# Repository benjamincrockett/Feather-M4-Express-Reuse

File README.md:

Index	Manufacturer Part Number	Manufacturer Name	Description	Lead Time	Availability	Stock Status	Attrition %	Requested Quantity 1	Pack Quantity 1	Pack Type 1	Digi-Key Part Number 1	Unit Price 1	Extended Price 1	Minimum Order Quantity 1	Customer Reference	Requested Part Number
1	    YC164-JR-07100KL	YAGEO	RES ARRAY 4 RES 100K OHM 1206		170,122	In Stock		1	1	Cut Tape (CT)	YC164J-100KCT-ND	0.10000	$0.10	1		YC164J-100KTR-ND
2	    DMP2045U-7	Diodes Incorporated	MOSFET P-CH 20V 4.3A SOT23		65,562	In Stock		1	1	Cut Tape (CT)	DMP2045U-7DICT-ND	0.17000	$0.17	1		DMP2045U-7DITR-ND
3	    MBR120VLSFT1G	onsemi	DIODE SCHOTTKY 20V 1A SOD123FL		110,035	In Stock		1	1	Cut Tape (CT)	MBR120VLSFT1GOSCT-ND	0.41000	$0.41	1		MBR120VLSFT1GOSTR-ND
4	    ABS07-32.768KHZ-T	Abracon LLC	CRYSTAL 32.7680KHZ 12.5PF SMD		938,078	In Stock		1	1	Cut Tape (CT)	535-9542-1-ND	0.61000	$0.61	1		535-9542-1-ND
5	    USB4105-GF-A	GCT	CONN RCP USB2.0 TYP C 24P SMD RA		23,931	In Stock		1	1	Cut Tape (CT)	2073-USB4105-GF-ACT-ND	0.78000	$0.78	1		2073-USB4105-GF-ACT-ND
6	    C0603C220J5GACTU	KEMET	CAP CER 22PF 50V C0G/NP0 0603		127,396	In Stock		2	2	Cut Tape (CT)	399-C0603C220J5GACTUCT-ND	0.12000	$0.24	1		399-C0603C220J5GACTUCT-ND
7	    C0805C106K8RACTU	KEMET	CAP CER 10UF 10V X7R 0805		615,848	In Stock		5	5	Cut Tape (CT)	399-C0805C106K8RACTUCT-ND	0.38000	$1.90	1		399-C0805C106K8RACTUCT-ND
8	    C0603C105K4RACTU	KEMET	CAP CER 1UF 16V X7R 0603		16,549	In Stock		6	6	Cut Tape (CT)	399-C0603C105K4RACTUCT-ND	0.08000	$0.48	1		399-C0603C105K4RACTUCT-ND
9	    LSQNA251818T100K	Taiyo Yuden	FIXED IND 10UH 820MA 325MOHM SMD		2,400	In Stock		1	1	Cut Tape (CT)	587-LSQNA251818T100KCT-ND	0.12000	$0.12	1		587-LSQNA251818T100KCT-ND
10	  RT0603FRE071KL	YAGEO	RES SMD 1K OHM 1% 1/10W 0603		146,547	In Stock		1	1	Cut Tape (CT)	YAG2323CT-ND	0.10000	$0.10	1		YAG2323CT-ND
11	  RC0603FR-075K1L	YAGEO	RES 5.1K OHM 1% 1/10W 0603		755,466	In Stock		3	3	Cut Tape (CT)	311-5.10KHRCT-ND	0.10000	$0.30	1		311-5.10KHRCT-ND
12	  AT0603FRE0710KL	YAGEO	RES SMD 10K OHM 1% 1/10W 0603		22,095	In Stock		5	5	Cut Tape (CT)	YAG2122CT-ND	0.10000	$0.50	1		YAG2122CT-ND
13	  AT0603FRE072K2L	YAGEO	RES SMD 2.2K OHM 1% 1/10W 0603		1,520	In Stock		1	1	Cut Tape (CT)	YAG2127CT-ND	0.16000	$0.16	1		YAG2127CT-ND
14	  Y78B21110FP	C&K	SWITCH TACTILE SPST-NO 0.05A 32V		136,536	In Stock		1	1	Cut Tape (CT)	401-1426-1-ND	0.59000	$0.59	1		401-1426-1-ND
15	  ATSAMD51J19A-MUT	Microchip Technology	IC MCU 32BIT 512KB FLASH 64VQFN		3,462	In Stock		1	1	Cut Tape (CT)	ATSAMD51J19A-MUTCT-ND	5.90000	$5.90	1		ATSAMD51J19A-MUTCT-ND
16	  MCP73831T-2ACI/OT	Microchip Technology	IC BATT CNTL LI-ION 1CEL SOT23-5	1 expected in stock on 10-Nov-2025	0	Normally Stocking		1	1	Cut Tape (CT)	MCP73831T-2ACI/OTCT-ND	0.76000	$0.76	1		MCP73831T-2ACI/OTCT-ND
17	AP2112K-3.3TRG1	Diodes Incorporated	IC REG LINEAR 3.3V 600MA SOT-25		34,831	In Stock		1	1	Cut Tape (CT)	AP2112K-3.3TRG1DICT-ND	0.22000	$0.22	1		AP2112K-3.3TRG1DICT-ND
18	S2B-PH-SM4-TB	JST Sales America Inc.	CONN HEADER SMD R/A 2POS 2MM		81,304	In Stock		1	1	Cut Tape (CT)	455-S2B-PH-SM4-TBCT-ND	0.48000	$0.48	1		455-S2B-PH-SM4-TBCT-ND
19	BM03B-SRSS-TB	JST Sales America Inc.	CONN HEADER SMD 3POS 1MM		5,309	In Stock		1	1	Cut Tape (CT)	455-BM03B-SRSS-TBCT-ND	0.45000	$0.45	1		455-BM03B-SRSS-TBCT-ND
20	SM03B-SRSS-TB	JST Sales America Inc.	CONN HEADER SMD R/A 3POS 1MM		19,673	In Stock		1	1	Cut Tape (CT)	455-SM03B-SRSS-TBCT-ND	0.44000	$0.44	1		455-SM03B-SRSS-TBCT-ND
21	SM04B-SRSS-TB	JST Sales America Inc.	CONN HEADER SMD R/A 4POS 1MM		37,322	In Stock		1	1	Cut Tape (CT)	455-SM04B-SRSS-TBCT-ND	0.50000	$0.50	1		455-SM04B-SRSS-TBCT-ND
22	KO EELP41.22-Q1S2-25-A8J8-020-R18	ams-OSRAM USA INC.	LED ORANGE DIFFUSED 0603 SMD		23,602	In Stock		1	1	Cut Tape (CT)	475-KOEELP41.22-Q1S2-25-A8J8-020-R18CT-ND	0.14000	$0.14	1		475-KOEELP41.22-Q1S2-25-A8J8-020-R18CT-ND
23	KR EELP41.22-Q1S1-36-A8J8-020-R18	ams-OSRAM USA INC.	LED RED DIFFUSED 0603 SMD		11,725	In Stock		1	1	Cut Tape (CT)	475-KREELP41.22-Q1S1-36-A8J8-020-R18CT-ND	0.14000	$0.14	1		475-KREELP41.22-Q1S1-36-A8J8-020-R18CT-ND
24	KT EELP41.12-S2U1-25-2X4Y-5-R18	ams-OSRAM USA INC.	LED GREEN DIFFUSED 0603 SMD		26,710	In Stock		1	1	Cut Tape (CT)	475-KTEELP41.12-S2U1-25-2X4Y-5-R18CT-ND	0.16000	$0.16	1		475-KTEELP41.12-S2U1-25-2X4Y-5-R18CT-ND
25	W25Q128JVSIQ TR	Winbond Electronics	IC FLASH 128MBIT SPI/QUAD 8SOIC		117,652	In Stock		1	1	Cut Tape (CT)	256-W25Q128JVSIQTRCT-ND	1.85000	$1.85	1		256-W25Q128JVSIQTRCT-ND
26	RMCF0603FT100R	Stackpole Electronics Inc	RES 100 OHM 1% 1/10W 0603		1,052,511	In Stock		2	2	Cut Tape (CT)	RMCF0603FT100RCT-ND	0.10000	$0.20	1		RMCF0603FT100RCT-ND
27	CRT0603-BY-1003ELF	Bourns Inc.	RES SMD 100K OHM 0.1% 1/10W 0603		206,819	In Stock		3	3	Cut Tape (CT)	CRT0603-BY-1003ELFCT-ND	0.10000	$0.30	1		CRT0603-BY-1003ELFCT-ND

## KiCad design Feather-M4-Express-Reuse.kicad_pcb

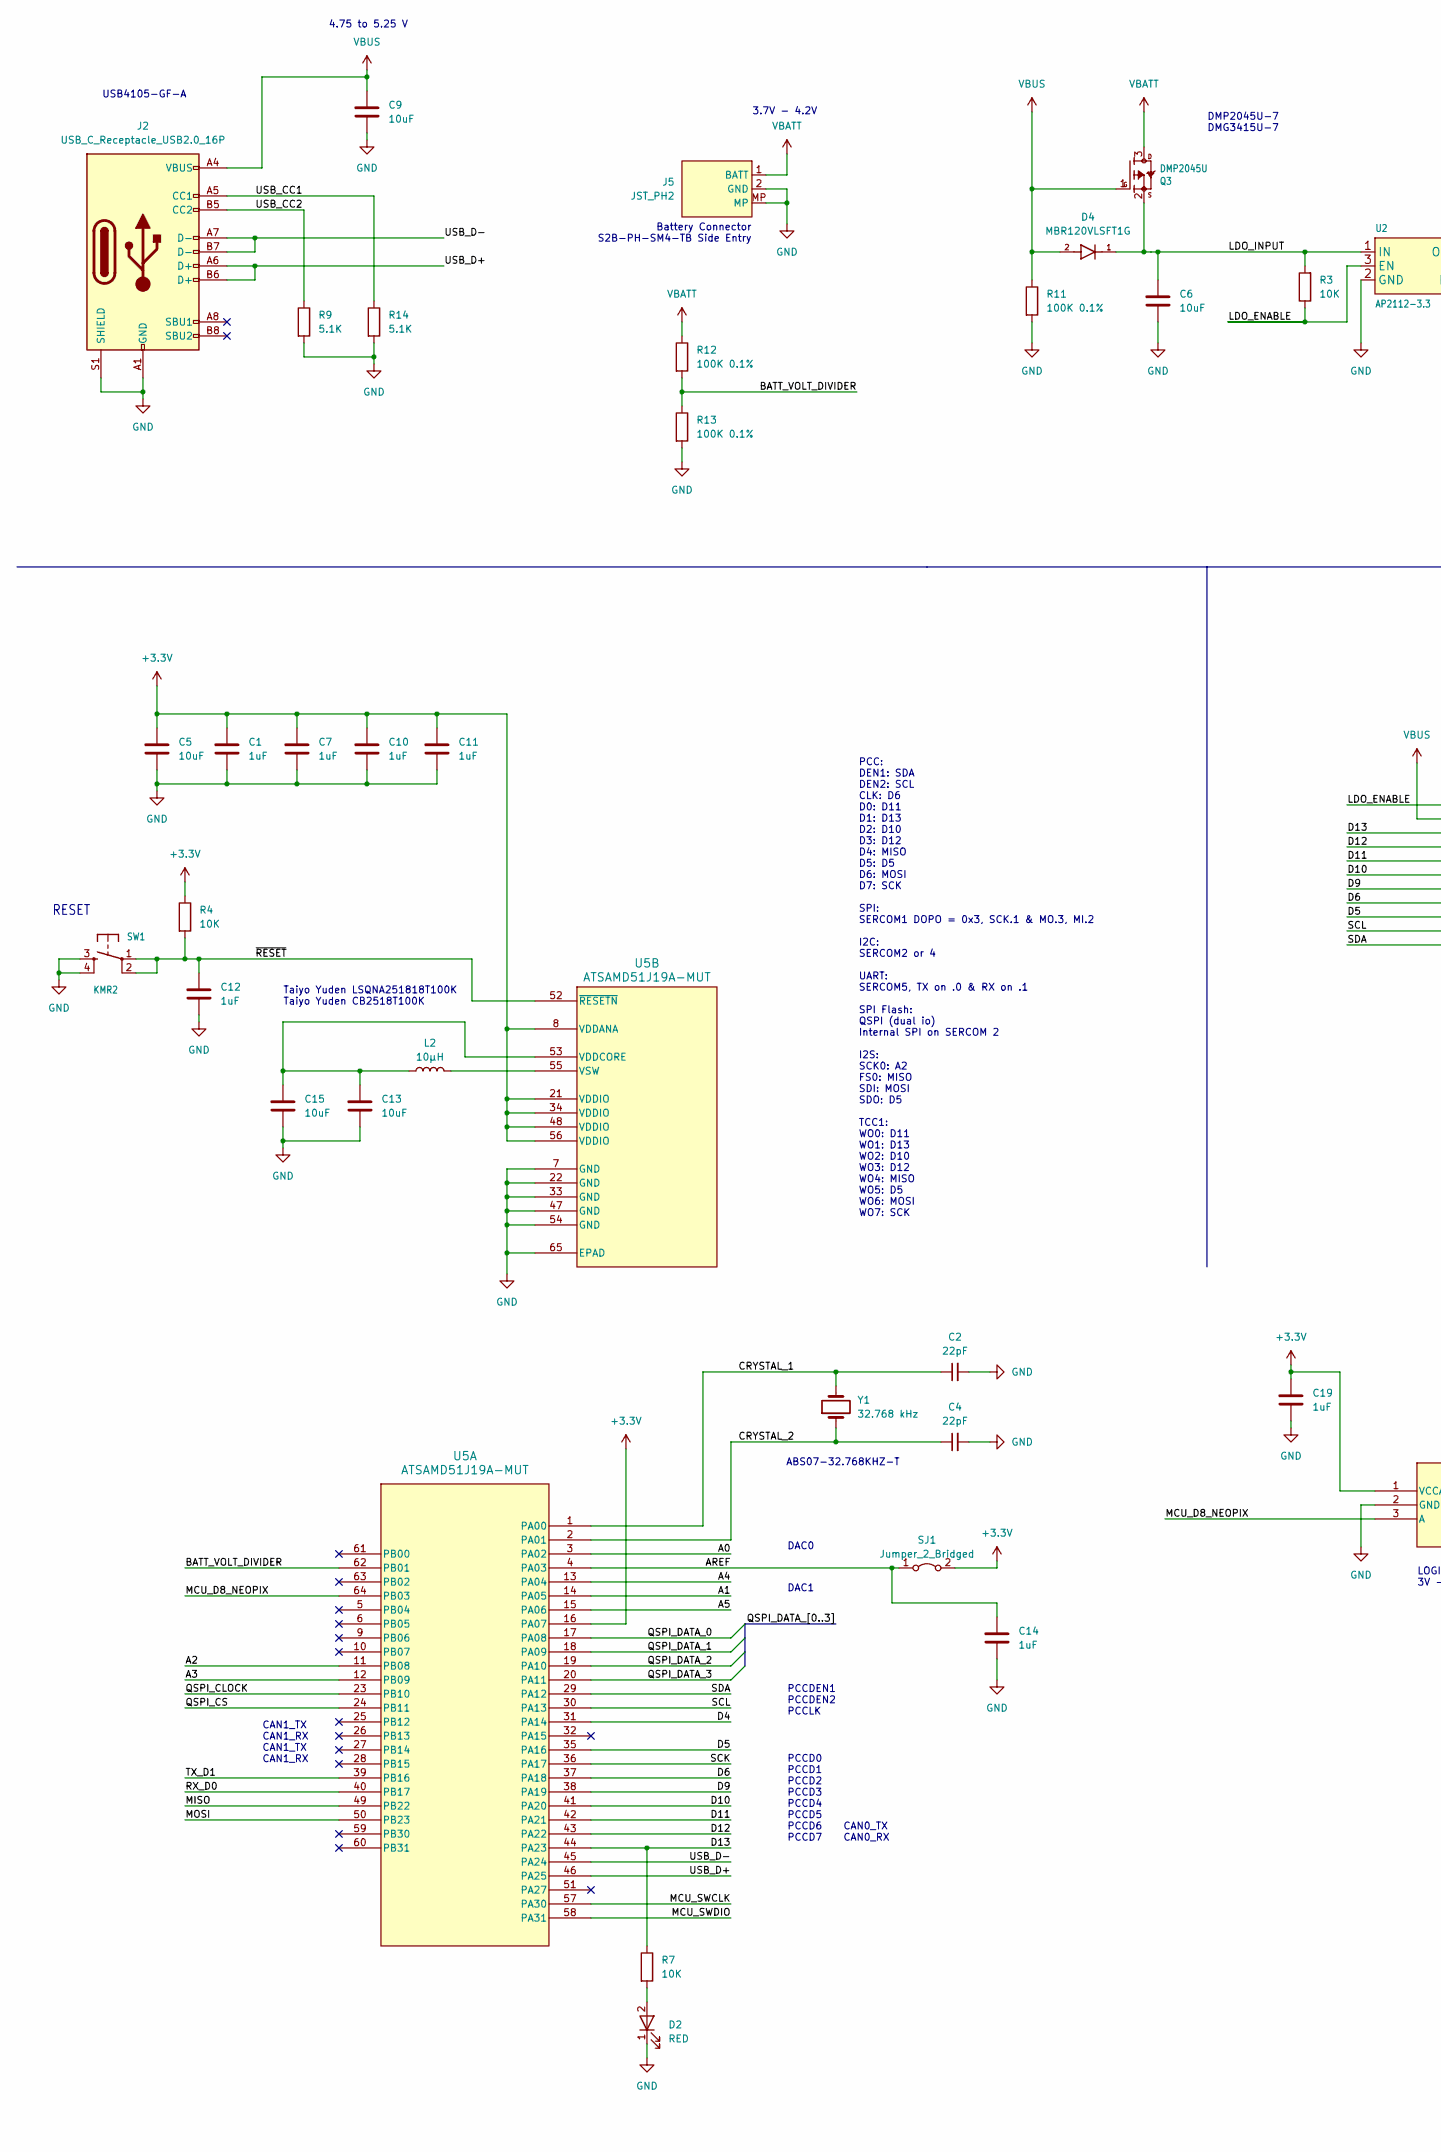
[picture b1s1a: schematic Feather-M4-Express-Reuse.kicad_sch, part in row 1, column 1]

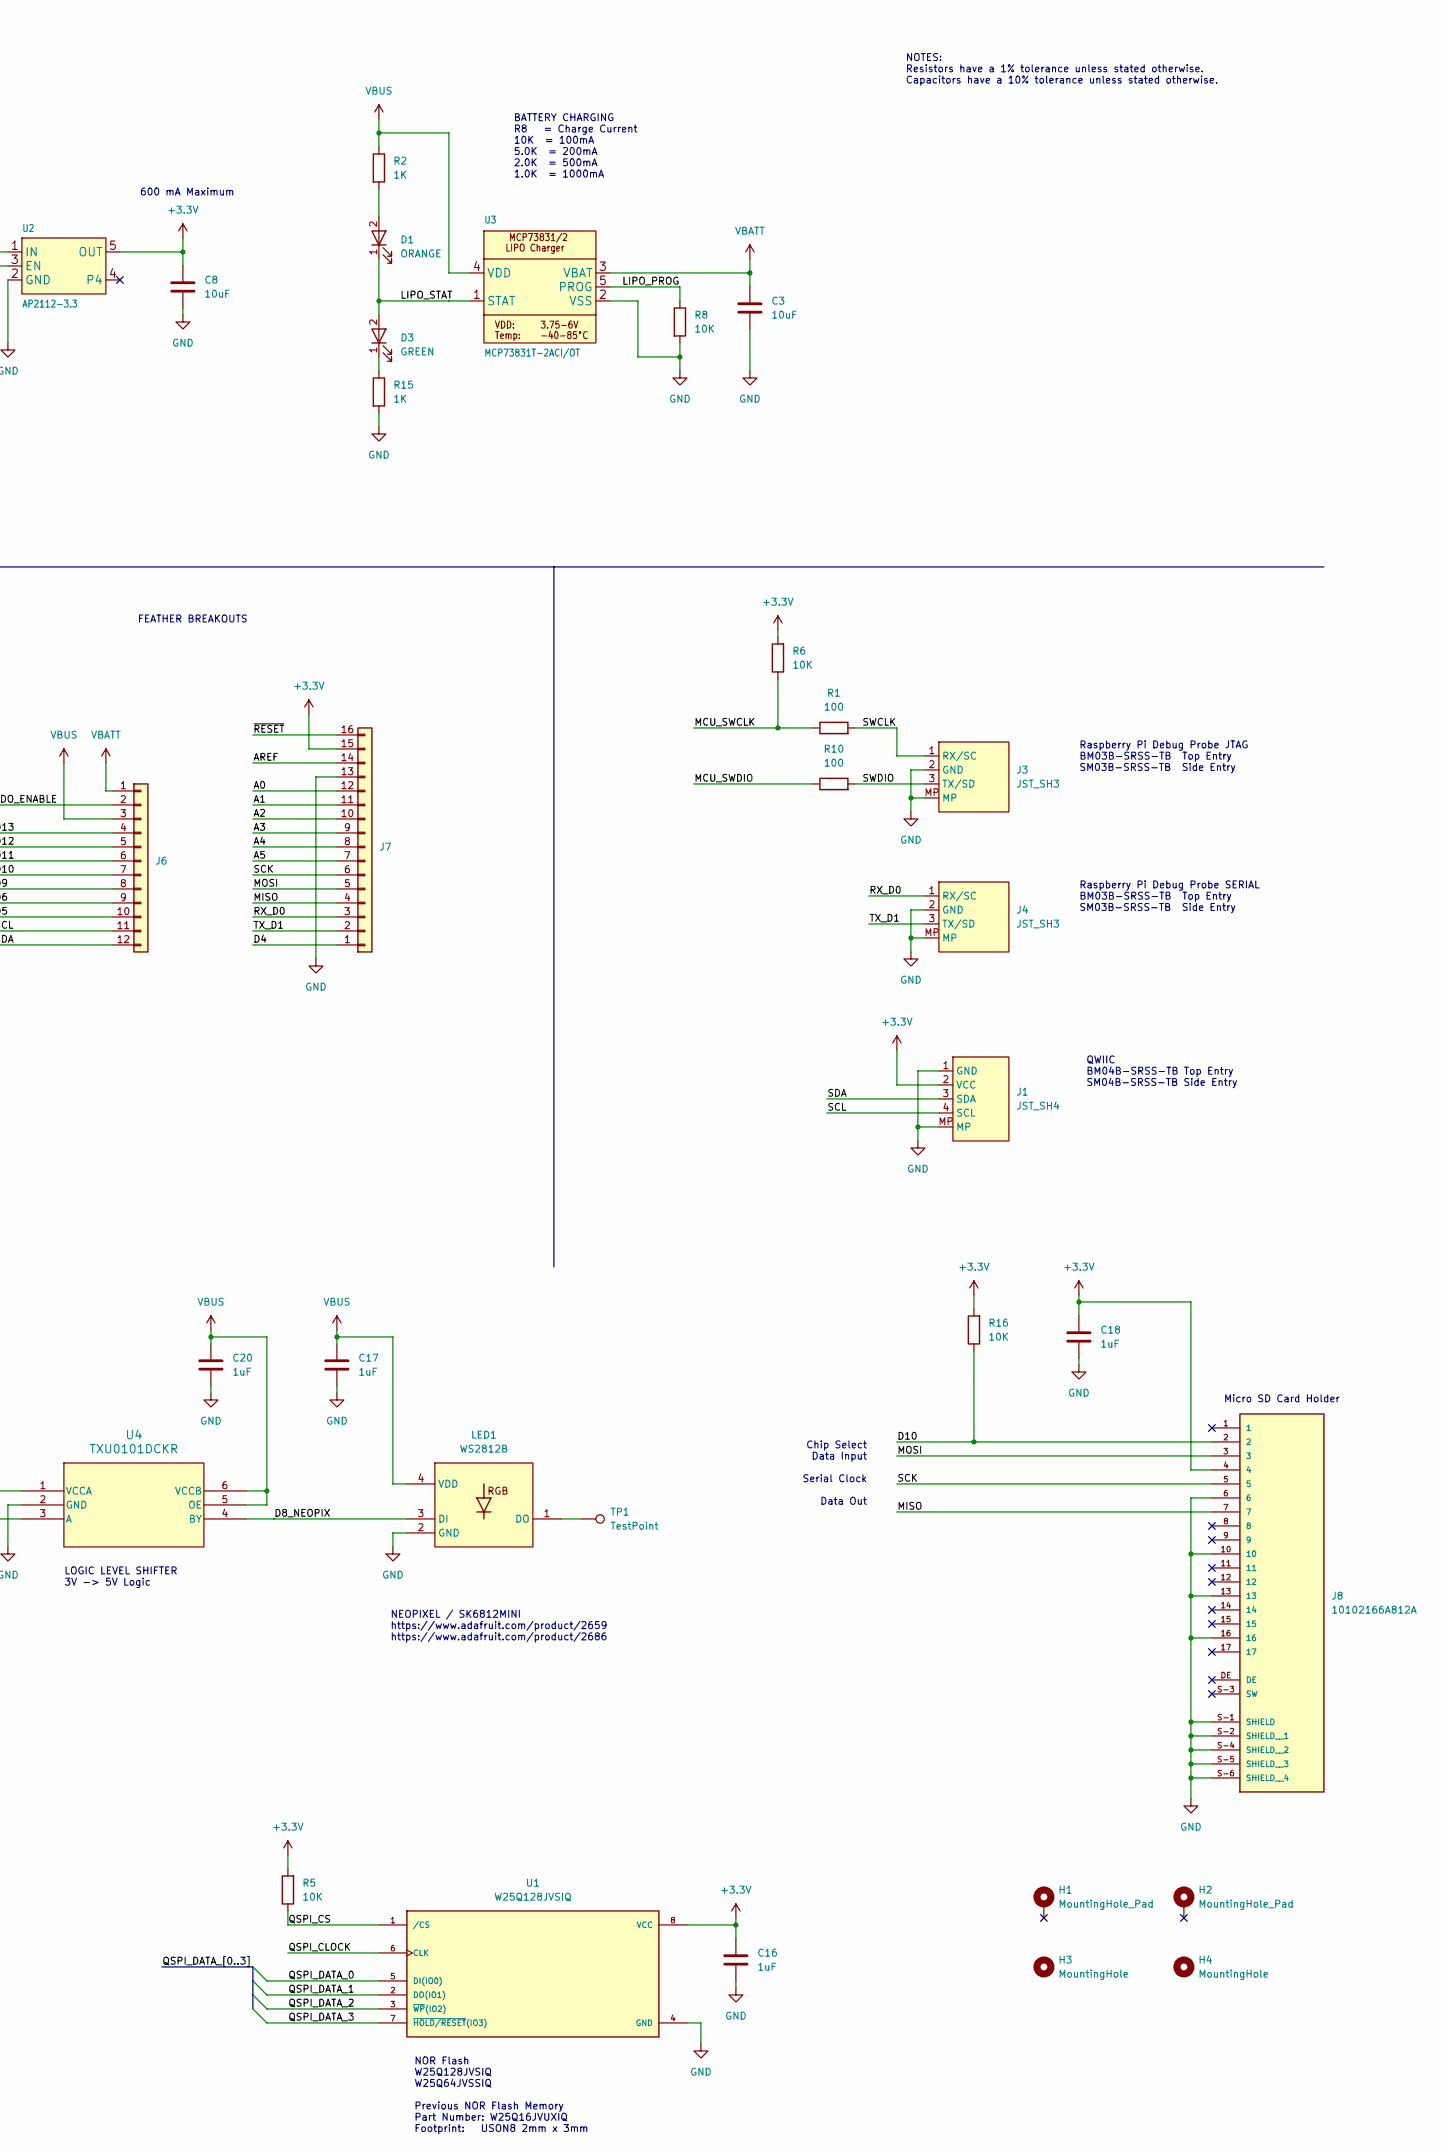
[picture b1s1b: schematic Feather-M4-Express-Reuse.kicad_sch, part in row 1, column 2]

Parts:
C1, C7, C10, C11, C12, C14, C16, C17, C18, C19, C20: 1uF; C_0603_1608Metric_Pad1.08x0.95mm_HandSolder
C2, C4: 22pF; C_0603_1608Metric_Pad1.08x0.95mm_HandSolder
C3, C5, C6, C8, C9, C13, C15: 10uF; C_0805_2012Metric_Pad1.18x1.45mm_HandSolder
D1: ORANGE; D_0603_1608Metric_Pad1.05x0.95mm_HandSolder
D2: RED; LED_0603_1608Metric_Pad1.05x0.95mm_HandSolder
D3: GREEN; D_0603_1608Metric_Pad1.05x0.95mm_HandSolder
D4: MBR120VLSFT1G; DIOM3616X98N; PARTREV 5/10/2013
H1, H2: MountingHole_Pad; MOUNTINGHOLE_2.5_PLATED
H3, H4: MountingHole; UNPLATED_HOLE_100MIL
J1: JST_SH4; JST_SH_SM04B-SRSS-TB_1x04-1MP_P1.00mm_Horizontal
J2: USB_C_Receptacle_USB2.0_16P; USB_C_Receptacle_GCT_USB4105-xx-A_16P_TopMnt_Horizontal
J3, J4: JST_SH3; JST_SH_BM03B-SRSS-TB_1x03-1MP_P1.00mm_Vertical
J5: JST_PH2; JST_PH_S2B-PH-SM4-TB_1x02-1MP_P2.00mm_Horizontal
J6: Conn_01x12; 1X12_ROUND
J7: Conn_01x16; 1X16_ROUND
J8: 10102166A812A; AMPHENOL_10102166A812A; PARTREV 7
L2: 10µH; INDUCTOR_1007
LED1: WS2812B; LED3535
Q3: DMP2045U; SOT-23_DIO
R1, R10: 100; R_0603_1608Metric_Pad0.98x0.95mm_HandSolder
R2, R15: 1K; R_0603_1608Metric_Pad0.98x0.95mm_HandSolder
R3, R4, R5, R6, R7, R8, R16: 10K; R_0603_1608Metric_Pad0.98x0.95mm_HandSolder
R9, R14: 5.1K; R_0603_1608Metric_Pad0.98x0.95mm_HandSolder
R11, R12, R13: 100K 0.1%; R_0603_1608Metric_Pad0.98x0.95mm_HandSolder
SJ1: Jumper_2_Bridged; SolderJumper-2_P1.3mm_Bridged_Pad1.0x1.5mm
SW1: KMR2; BTN_KMR2_4.6X2.8
TP1: TestPoint; TestPoint_Pad_D1.0mm
U1: W25Q128JVSIQ; SOIC_128JVSIQ_WIN-M; PARTREV I
U2: AP2112-3.3; SOT_RG1_DIO
U3: MCP73831T-2ACI/OT; SOT-23-5_MC_MCH-M
U4: TXU0101DCKR; SC70-6_DCK_TEX-M
U5: ATSAMD51J19A-MUT; QFN64_9x9MC_MCH-M_Modified
Y1: 32.768 kHz; XTAL3215

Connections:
+3.3V: C1.1, C5.1, C7.1, C8.1, C10.1, C11.1, C16.1, C18.1, C19.1, J1.2 (VCC), J7.15, J8.4, R4.1, R5.2, R6.2, R16.2, SJ1.2 (B), U1.8 (VCC), U2.5 (OUT), U4.1 (VCCA), U5.8 (VDDANA), U5.16 (PA07), U5.21 (VDDIO), U5.34 (VDDIO), U5.48 (VDDIO), U5.56 (VDDIO)
/A0: J7.12, U5.3 (PA02)
/A1: J7.11, U5.14 (PA05)
/A2: J7.10, U5.11 (PB08)
/A3: J7.9, U5.12 (PB09)
/A4: J7.8, U5.13 (PA04)
/A5: J7.7, U5.15 (PA06)
/AREF: C14.1, J7.14, SJ1.1 (A), U5.4 (PA03)
/BATT_VOLT_DIVIDER: R12.2, R13.1, U5.62 (PB01)
/CRYSTAL_1: C2.1, U5.1 (PA00), Y1.2
/CRYSTAL_2: C4.1, U5.2 (PA01), Y1.1
/D4: J7.1, U5.31 (PA14)
/D5: J6.10, U5.35 (PA16)
/D6: J6.9, U5.37 (PA18)
/D8_NEOPIX: LED1.3 (DI), U4.4 (BY)
/D9: J6.8, U5.38 (PA19)
/D10: J6.7, J8.2, R16.1, U5.41 (PA20)
/D11: J6.6, U5.42 (PA21)
/D12: J6.5, U5.43 (PA22)
/D13: J6.4, R7.1, U5.44 (PA23)
/LDO_ENABLE: J6.2, R3.1, U2.3 (EN)
/LDO_INPUT: C6.1, D4.1, Q3.2 (S), R3.2, U2.1 (IN)
/LIPO_PROG: R8.1, U3.5 (PROG)
/LIPO_STAT: D1.1 (K), D3.2 (A), U3.1 (STAT)
/MCU_D8_NEOPIX: U4.3 (A), U5.64 (PB03)
/MCU_SWCLK: R1.1, R6.1, U5.57 (PA30)
/MCU_SWDIO: R10.1, U5.58 (PA31)
/MISO: J7.4, J8.7, U5.49 (PB22)
/MOSI: J7.5, J8.3, U5.50 (PB23)
/QSPI_CLOCK: U1.6 (CLK), U5.23 (PB10)
/QSPI_CS: R5.1, U1.1 (/CS), U5.24 (PB11)
/QSPI_DATA_0: U1.5 (DI(IO0)), U5.17 (PA08)
/QSPI_DATA_1: U1.2 (DO(IO1)), U5.18 (PA09)
/QSPI_DATA_2: U1.3 (~WP(IO2)), U5.19 (PA10)
/QSPI_DATA_3: U1.7 (~HOLD/RESET(IO3)), U5.20 (PA11)
/RX_D0: J4.1 (RX/SC), J7.3, U5.40 (PB17)
/SCK: J7.6, J8.5, U5.36 (PA17)
/SCL: J1.4 (SCL), J6.11, U5.30 (PA13)
/SDA: J1.3 (SDA), J6.12, U5.29 (PA12)
/SWCLK: J3.1 (RX/SC), R1.2
/SWDIO: J3.3 (TX/SD), R10.2
/TX_D1: J4.3 (TX/SD), J7.2, U5.39 (PB16)
/USB_CC1: J2.A5 (CC1), R14.1
/USB_CC2: J2.B5 (CC2), R9.1
/USB_D+: J2.A6 (D+), J2.B6 (D+), U5.46 (PA25)
/USB_D-: J2.A7 (D-), J2.B7 (D-), U5.45 (PA24)
/~RESET: C12.2, J7.16, R4.2, SW1.1, SW1.2 (P1), U5.52 (~RESETN)
GND: C1.2, C2.2, C3.2, C4.2, C5.2, C6.2, C7.2, C8.2, C9.2, C10.2, C11.2, C12.1, C13.2, C14.2, C15.2, C16.2, C17.2, C18.2, C19.2, C20.2, D2.1 (K), J1.1 (GND), J1.MP, J2.A1 (GND), J2.A12 (GND), J2.B1 (GND), J2.B12 (GND), J2.S1 (SHIELD), J3.2 (GND), J3.MP, J4.2 (GND), J4.MP, J5.2 (GND), J5.MP, J7.13, J8.6, J8.10, J8.13, J8.16, J8.S-1 (SHIELD), J8.S-2 (SHIELD__1), J8.S-4 (SHIELD__2), J8.S-5 (SHIELD__3), J8.S-6 (SHIELD__4), LED1.2 (GND), R8.2, R9.2, R11.2, R13.2, R14.2, R15.2, SW1.3 (S), SW1.4 (S1), U1.4 (GND), U2.2 (GND), U3.2 (VSS), U4.2 (GND), U5.7 (GND), U5.22 (GND), U5.33 (GND), U5.47 (GND), U5.54 (GND), U5.65 (EPAD)
unnamed: D1.2 (A), R2.2
unnamed: D2.2 (A), R7.2
unnamed: D3.1 (K), R15.1
unnamed: LED1.1 (DO), TP1.1
unnamed: C13.1, C15.1, L2.1, U5.53 (VDDCORE)
unnamed: L2.2, U5.55 (VSW)
VBATT: C3.1, J5.1 (BATT), J6.1, Q3.3 (D), R12.1, U3.3 (VBAT)
VBUS: C9.1, C17.1, C20.1, D4.2, J2.A4 (VBUS), J2.A9 (VBUS), J2.B4 (VBUS), J2.B9 (VBUS), J6.3, LED1.4 (VDD), Q3.1 (G), R2.1, R11.1, U3.4 (VDD), U4.5 (OE), U4.6 (VCCB)

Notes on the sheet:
PCCD0 PCCD1 PCCD2 PCCD3 PCCD4 PCCD5 PCCD6 CAN0_TX PCCD7 CAN0_RX
600 mA Maximum
Raspberry Pi Debug Probe JTAG BM03B-SRSS-TB Top Entry SM03B-SRSS-TB Side Entry
Battery Connector S2B-PH-SM4-TB Side Entry
FEATHER BREAKOUTS
PCC: DEN1: SDA DEN2: SCL CLK: D6 D0: D11 D1: D13 D2: D10 D3: D12 D4: MISO D5: D5 D6: MOSI D7: SCK SPI: SERCOM1 DOPO = 0x3, SCK.1 & MO.3, MI.2 I2C: SERCOM2 or 4 UART: SERCOM5, TX on .0 & RX on .1 SPI Flash: QSPI (dual io) Internal SPI on SERCOM 2 I2S: SCK0: A2 FS0: MISO SDI: MOSI SDO: D5 TCC1: WO0: 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
Taiyo Yuden LSQNA251818T100K Taiyo Yuden CB2518T100K
ABS07-32.768KHZ-T
4.75 to 5.25 V
DAC0
USB4105-GF-A
Chip Select Data Input Serial Clock Data Out
NOR Flash W25Q128JVSIQ W25Q64JVSSIQ Previous NOR Flash Memory Part Number: W25Q16JVUXIQ Footprint: USON8 2mm x 3mm
BATTERY CHARGING R8 = Charge Current 10K = 100mA 5.0K = 200mA 2.0K = 500mA 1.0K = 1000mA
Micro SD Card Holder
Raspberry Pi Debug Probe SERIAL BM03B-SRSS-TB Top Entry SM03B-SRSS-TB Side Entry
DAC1
DMP2045U-7 DMG3415U-7
NEOPIXEL / SK6812MINI https://www.adafruit.com/product/2659 https://www.adafruit.com/product/2686
CAN1_TX CAN1_RX CAN1_TX CAN1_RX
LOGIC LEVEL SHIFTER 3V -> 5V Logic
PCCDEN1 PCCDEN2 PCCLK
3.7V - 4.2V
NOTES: Resistors have a 1% tolerance unless stated otherwise. Capacitors have a 10% tolerance unless stated otherwise.
RESET
QWIIC BM04B-SRSS-TB Top Entry SM04B-SRSS-TB Side Entry

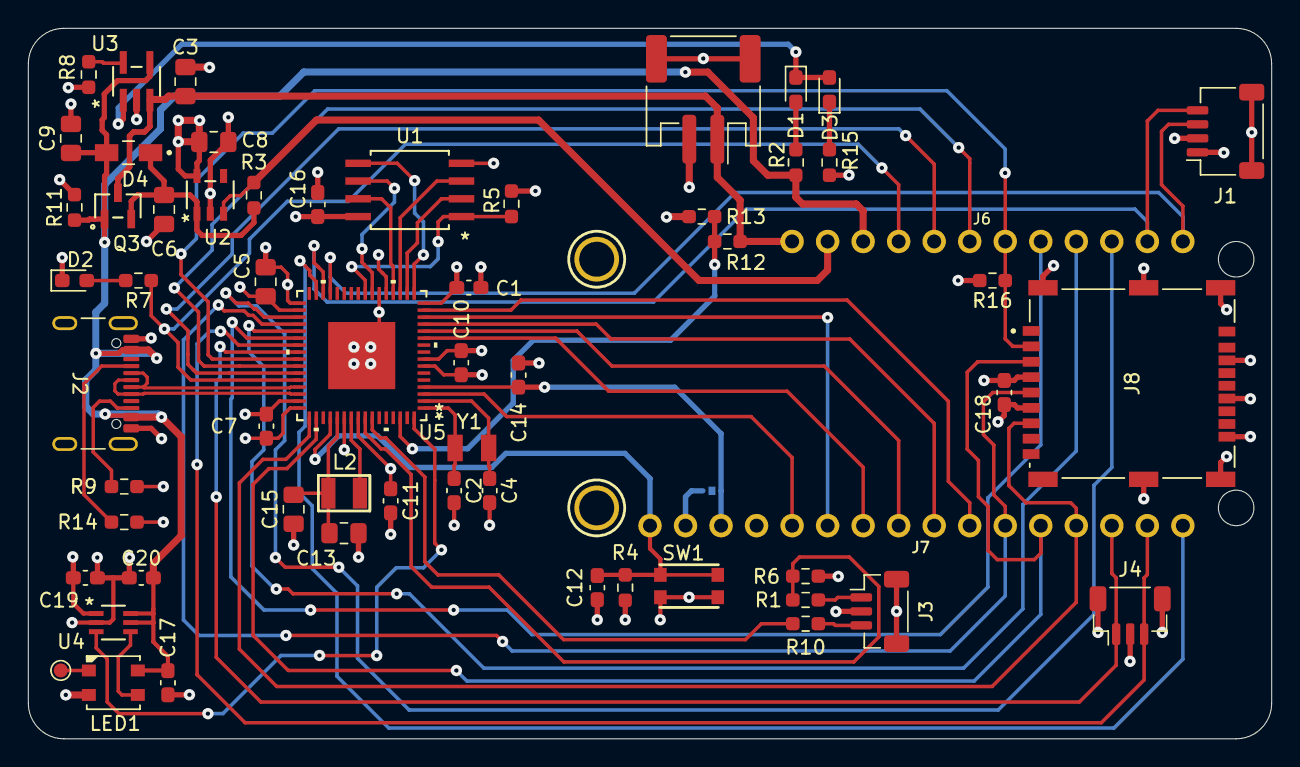
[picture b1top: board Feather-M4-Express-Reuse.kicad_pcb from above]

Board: 4 copper layers, 88.9 x 50.8 mm, 64 parts (1 on the bottom side), 56 nets.

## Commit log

2025-11-02 Initial commit.
2025-11-02 Add inventory list of electronic components to README
    Added a detailed inventory list of electronic components including part numbers, manufacturers, descriptions, lead times, and pricing.
2025-11-26 Latest Revision
